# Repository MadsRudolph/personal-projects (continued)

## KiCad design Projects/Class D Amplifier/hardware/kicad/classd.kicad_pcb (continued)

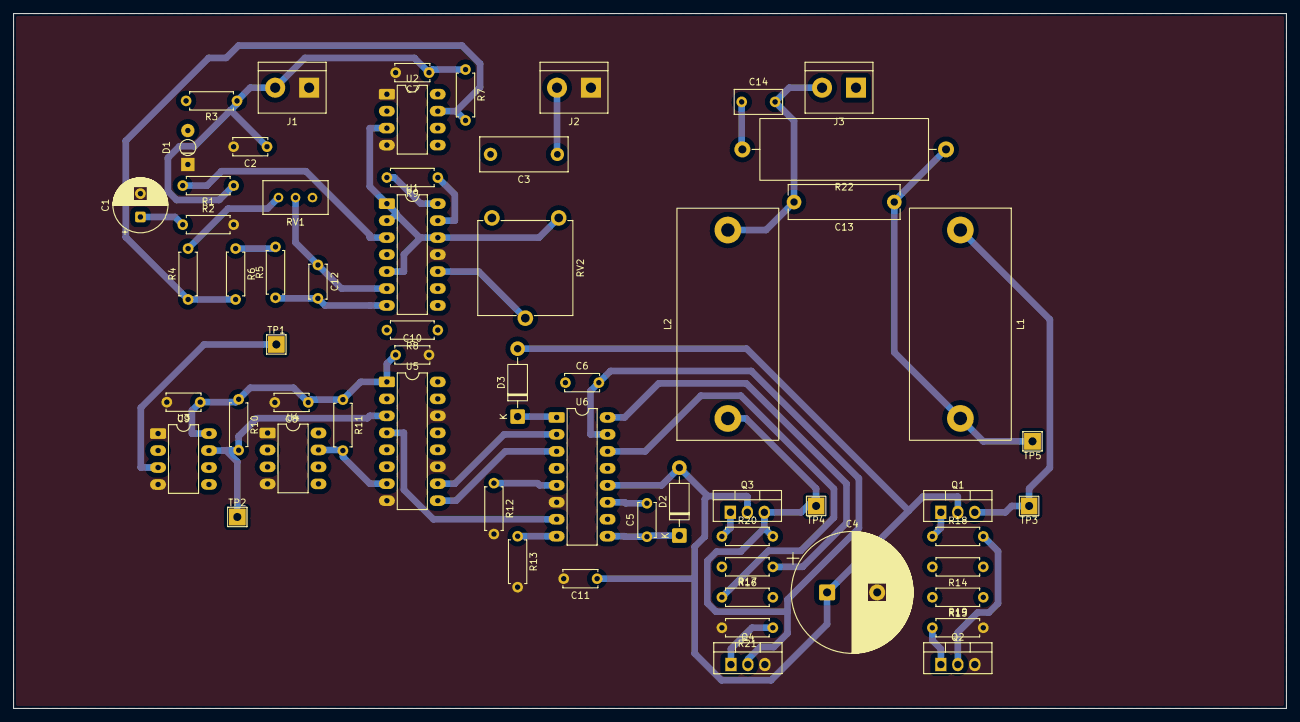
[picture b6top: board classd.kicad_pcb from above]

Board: 2 copper layers, 190.5 x 104.0 mm, 61 parts (0 on the bottom side), 39 nets.

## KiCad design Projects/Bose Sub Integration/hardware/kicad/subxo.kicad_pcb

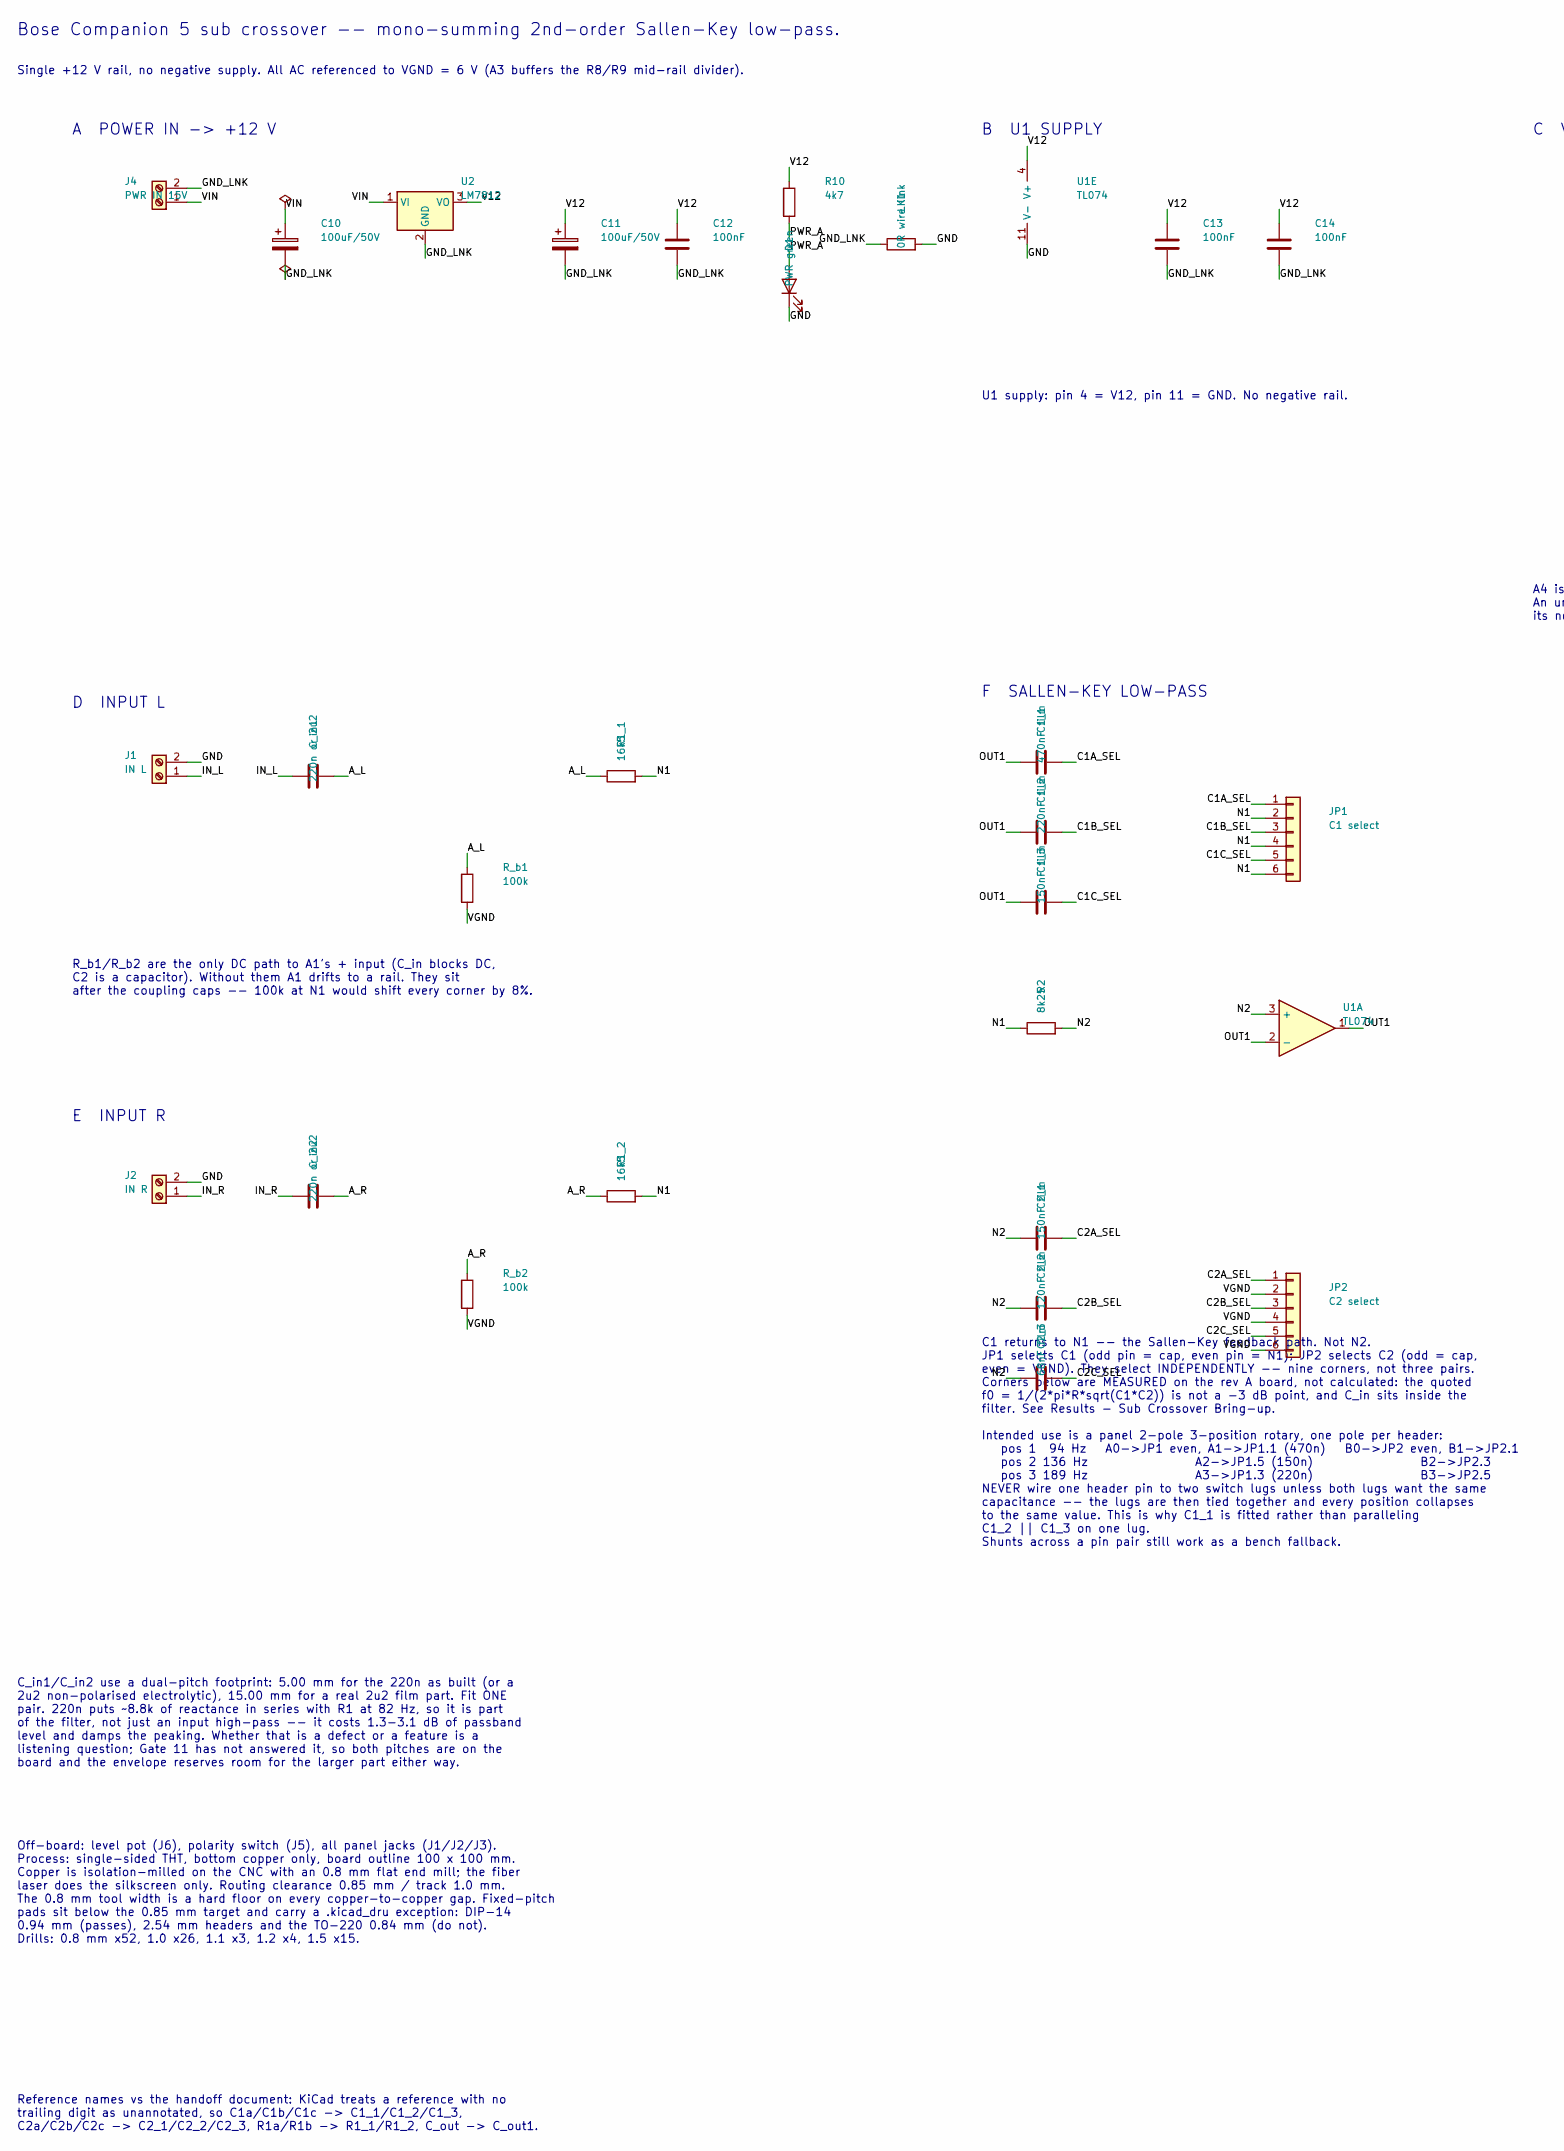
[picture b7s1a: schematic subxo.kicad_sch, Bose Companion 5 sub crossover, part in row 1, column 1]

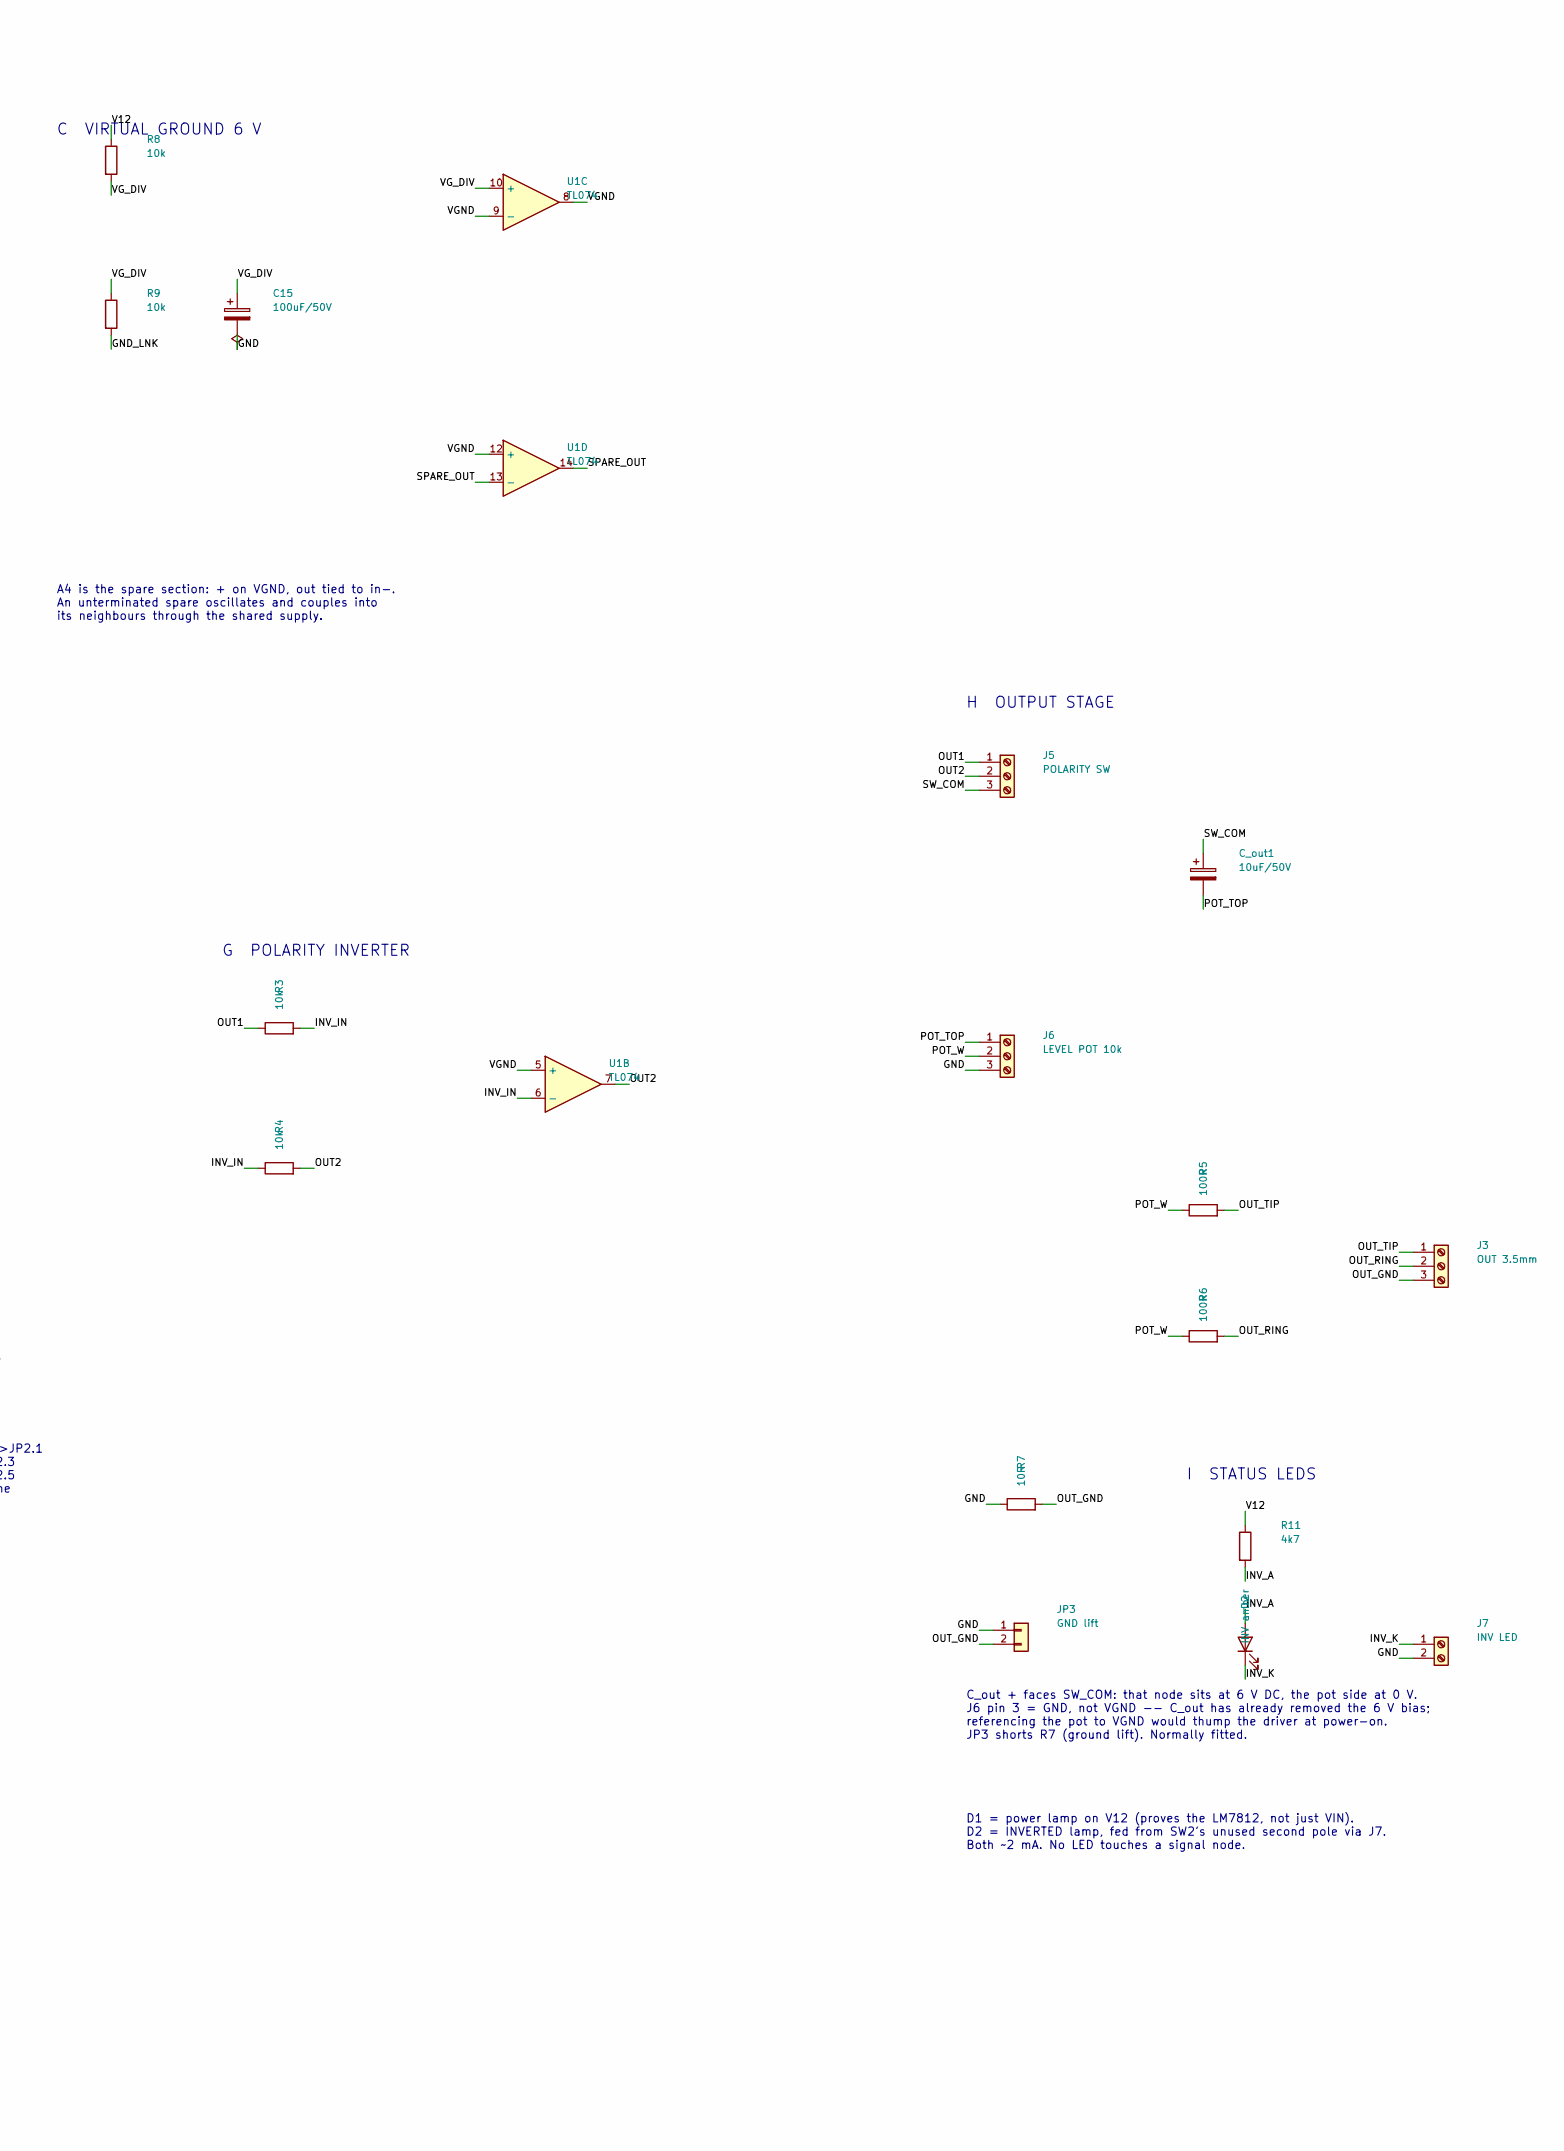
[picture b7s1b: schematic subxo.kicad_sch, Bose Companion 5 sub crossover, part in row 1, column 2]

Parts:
C1_1: 470nF film; C_Rect_L7.2mm_W3.0mm_P5.00mm_FKS2_FKP2_MKS2_MKP2
C1_2: 220nF film; C_Rect_L18.0mm_W7.0mm_P15.00mm_FKS3_FKP3
C1_3: 150nF film; C_Rect_L11.0mm_W4.2mm_P10.00mm_MKT
C2_1: 150nF film; C_Rect_L7.2mm_W5.5mm_P5.00mm_FKS2_FKP2_MKS2_MKP2
C2_2: 120nF film; C_Rect_L13.0mm_W4.0mm_P10.00mm_FKS3_FKP3_MKS4
C2_3: 68nF film; C_Rect_L7.2mm_W5.5mm_P5.00mm_FKS2_FKP2_MKS2_MKP2
C10, C11, C15: 100uF/50V; CP_Radial_D10.0mm_P5.00mm
C12, C13, C14: 100nF; C_Disc_D5.0mm_W2.5mm_P5.00mm
C_in1, C_in2: 220n or 2u2; C_Rect_L18.0mm_W9.0mm_P15.00mm_FKS3_FKP3
C_out1: 10uF/50V; CP_Radial_D8.0mm_P3.50mm
D1: PWR green; LED_D3.0mm
D2: INV amber; LED_D3.0mm
J1: IN L; TerminalBlock_bornier-2_P5.08mm
J2: IN R; TerminalBlock_bornier-2_P5.08mm
J3: OUT 3.5mm; TerminalBlock_bornier-3_P5.08mm
J4: PWR IN 15V; TerminalBlock_bornier-2_P5.08mm
J5: POLARITY SW; TerminalBlock_bornier-3_P5.08mm
J6: LEVEL POT 10k; TerminalBlock_bornier-3_P5.08mm
J7: INV LED; TerminalBlock_bornier-2_P5.08mm
JP1: C1 select; PinHeader_1x06_P2.54mm_Vertical
JP2: C2 select; PinHeader_1x06_P2.54mm_Vertical
JP3: GND lift; PinHeader_1x02_P2.54mm_Vertical
LK1: 0R wire link; WireLink_P14.50mm
R1_1, R1_2: 16k5; R_Axial_DIN0207_L6.3mm_D2.5mm_P7.62mm_Horizontal
R2: 8k25; R_Axial_DIN0207_L6.3mm_D2.5mm_P7.62mm_Horizontal
R3, R4, R8, R9: 10k; R_Axial_DIN0207_L6.3mm_D2.5mm_P7.62mm_Horizontal
R5, R6: 100R; R_Axial_DIN0207_L6.3mm_D2.5mm_P7.62mm_Horizontal
R7: 10R; R_Axial_DIN0207_L6.3mm_D2.5mm_P7.62mm_Horizontal
R10, R11: 4k7; R_Axial_DIN0207_L6.3mm_D2.5mm_P7.62mm_Horizontal
R_b1, R_b2: 100k; R_Axial_DIN0207_L6.3mm_D2.5mm_P7.62mm_Horizontal
U1: TL074; DIP-14_W7.62mm_LongPads
U2: LM7812; TO-220-3_Vertical_LaserPads

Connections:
/A_L: C_in1.2, R1_1.1, R_b1.1
/A_R: C_in2.2, R1_2.1, R_b2.1
/C1A_SEL: C1_1.2, JP1.1
/C1B_SEL: C1_2.2, JP1.3
/C1C_SEL: C1_3.2, JP1.5
/C2A_SEL: C2_1.2, JP2.1
/C2B_SEL: C2_2.2, JP2.3
/C2C_SEL: C2_3.2, JP2.5
/GND: C15.2, D1.1 (K), J1.2, J2.2, J6.3, J7.2, JP3.1, LK1.2, R7.1, U1.11 (V-)
/GND_LNK: C10.2, C11.2, C12.2, C13.2, C14.2, J4.2, LK1.1, R9.2, U2.2 (GND)
/INV_A: D2.2 (A), R11.2
/INV_IN: R3.2, R4.1, U1.6 (-)
/INV_K: D2.1 (K), J7.1
/IN_L: C_in1.1, J1.1
/IN_R: C_in2.1, J2.1
/N1: JP1.2, JP1.4, JP1.6, R1_1.2, R1_2.2, R2.1
/N2: C2_1.1, C2_2.1, C2_3.1, R2.2, U1.3 (+)
/OUT1: C1_1.1, C1_2.1, C1_3.1, J5.1, R3.1, U1.1, U1.2 (-)
/OUT2: J5.2, R4.2, U1.7
/OUT_GND: J3.3, JP3.2, R7.2
/OUT_RING: J3.2, R6.2
/OUT_TIP: J3.1, R5.2
/POT_TOP: C_out1.2, J6.1
/POT_W: J6.2, R5.1, R6.1
/PWR_A: D1.2 (A), R10.2
/SPARE_OUT: U1.13 (-), U1.14
/SW_COM: C_out1.1, J5.3
/V12: C11.1, C12.1, C13.1, C14.1, R8.1, R10.1, R11.1, U1.4 (V+), U2.3 (VO)
/VGND: JP2.2, JP2.4, JP2.6, R_b1.2, R_b2.2, U1.5 (+), U1.8, U1.9 (-), U1.12 (+)
/VG_DIV: C15.1, R8.2, R9.1, U1.10 (+)
/VIN: C10.1, J4.1, U2.1 (VI)

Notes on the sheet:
Bose Companion 5 sub crossover -- mono-summing 2nd-order Sallen-Key low-pass.
Single +12 V rail, no negative supply. All AC referenced to VGND = 6 V (A3 buffers the R8/R9 mid-rail divider).
A POWER IN -> +12 V
B U1 SUPPLY
C VIRTUAL GROUND 6 V
D INPUT L
E INPUT R
F SALLEN-KEY LOW-PASS
G POLARITY INVERTER
H OUTPUT STAGE
I STATUS LEDS
U1 supply: pin 4 = V12, pin 11 = GND. No negative rail.
A4 is the spare section: + on VGND, out tied to in-. An unterminated spare oscillates and couples into its neighbours through the shared supply.
R_b1/R_b2 are the only DC path to A1's + input (C_in blocks DC, C2 is a capacitor). Without them A1 drifts to a rail. They sit after the coupling caps -- 100k at N1 would shift every corner by 8%.
C1 returns to N1 -- the Sallen-Key feedback path. Not N2. JP1 selects C1 (odd pin = cap, even pin = N1); JP2 selects C2 (odd = cap, even = VGND). They select INDEPENDENTLY -- nine corners, not three pairs. Corners below are MEASURED on the rev A board, not calculated: the quoted f0 = 1/(2*pi*R*sqrt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
C_in1/C_in2 use a dual-pitch footprint: 5.00 mm for the 220n as built (or a 2u2 non-polarised electrolytic), 15.00 mm for a real 2u2 film part. Fit ONE pair. 220n puts ~8.8k of reactance in series with R1 at 82 Hz, so it is part of the filter, not just an input high-pass -- it costs 1.3-3.1 dB of p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
D1 = power lamp on V12 (proves the LM7812, not just VIN). D2 = INVERTED lamp, fed from SW2's unused second pole via J7. Both ~2 mA. No LED touches a signal node.
C_out + faces SW_COM: that node sits at 6 V DC, the pot side at 0 V. J6 pin 3 = GND, not VGND -- C_out has already removed the 6 V bias; referencing the pot to VGND would thump the driver at power-on. JP3 shorts R7 (ground lift). Normally fitted.
Off-board: level pot (J6), polarity switch (J5), all panel jacks (J1/J2/J3). Process: single-sided THT, bottom copper only, board outline 100 x 100 mm. Copper is isolation-milled on the CNC with an 0.8 mm flat end mill; the fiber laser does the silkscreen only. Routing clearance 0.85 mm / track 1.0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
Reference names vs the handoff document: KiCad treats a reference with no trailing digit as unannotated, so C1a/C1b/C1c -> C1_1/C1_2/C1_3, C2a/C2b/C2c -> C2_1/C2_2/C2_3, R1a/R1b -> R1_1/R1_2, C_out -> C_out1.

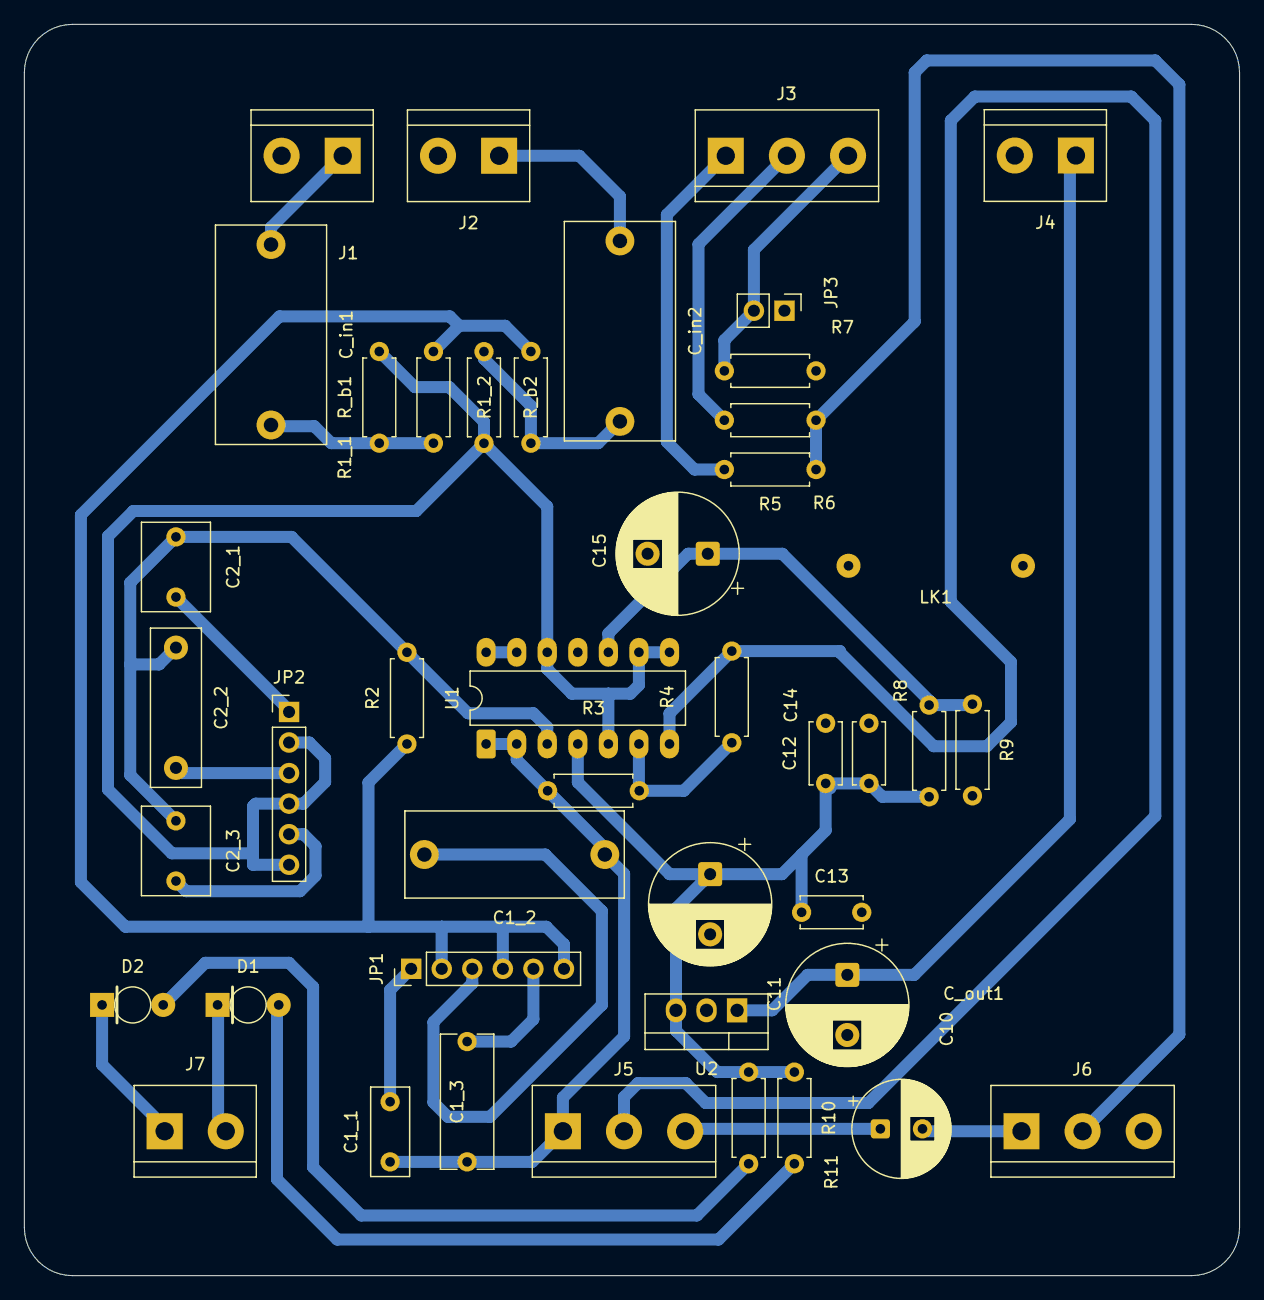
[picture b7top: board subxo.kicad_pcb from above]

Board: 2 copper layers, 101.0 x 104.0 mm, 44 parts (0 on the bottom side), 31 nets.

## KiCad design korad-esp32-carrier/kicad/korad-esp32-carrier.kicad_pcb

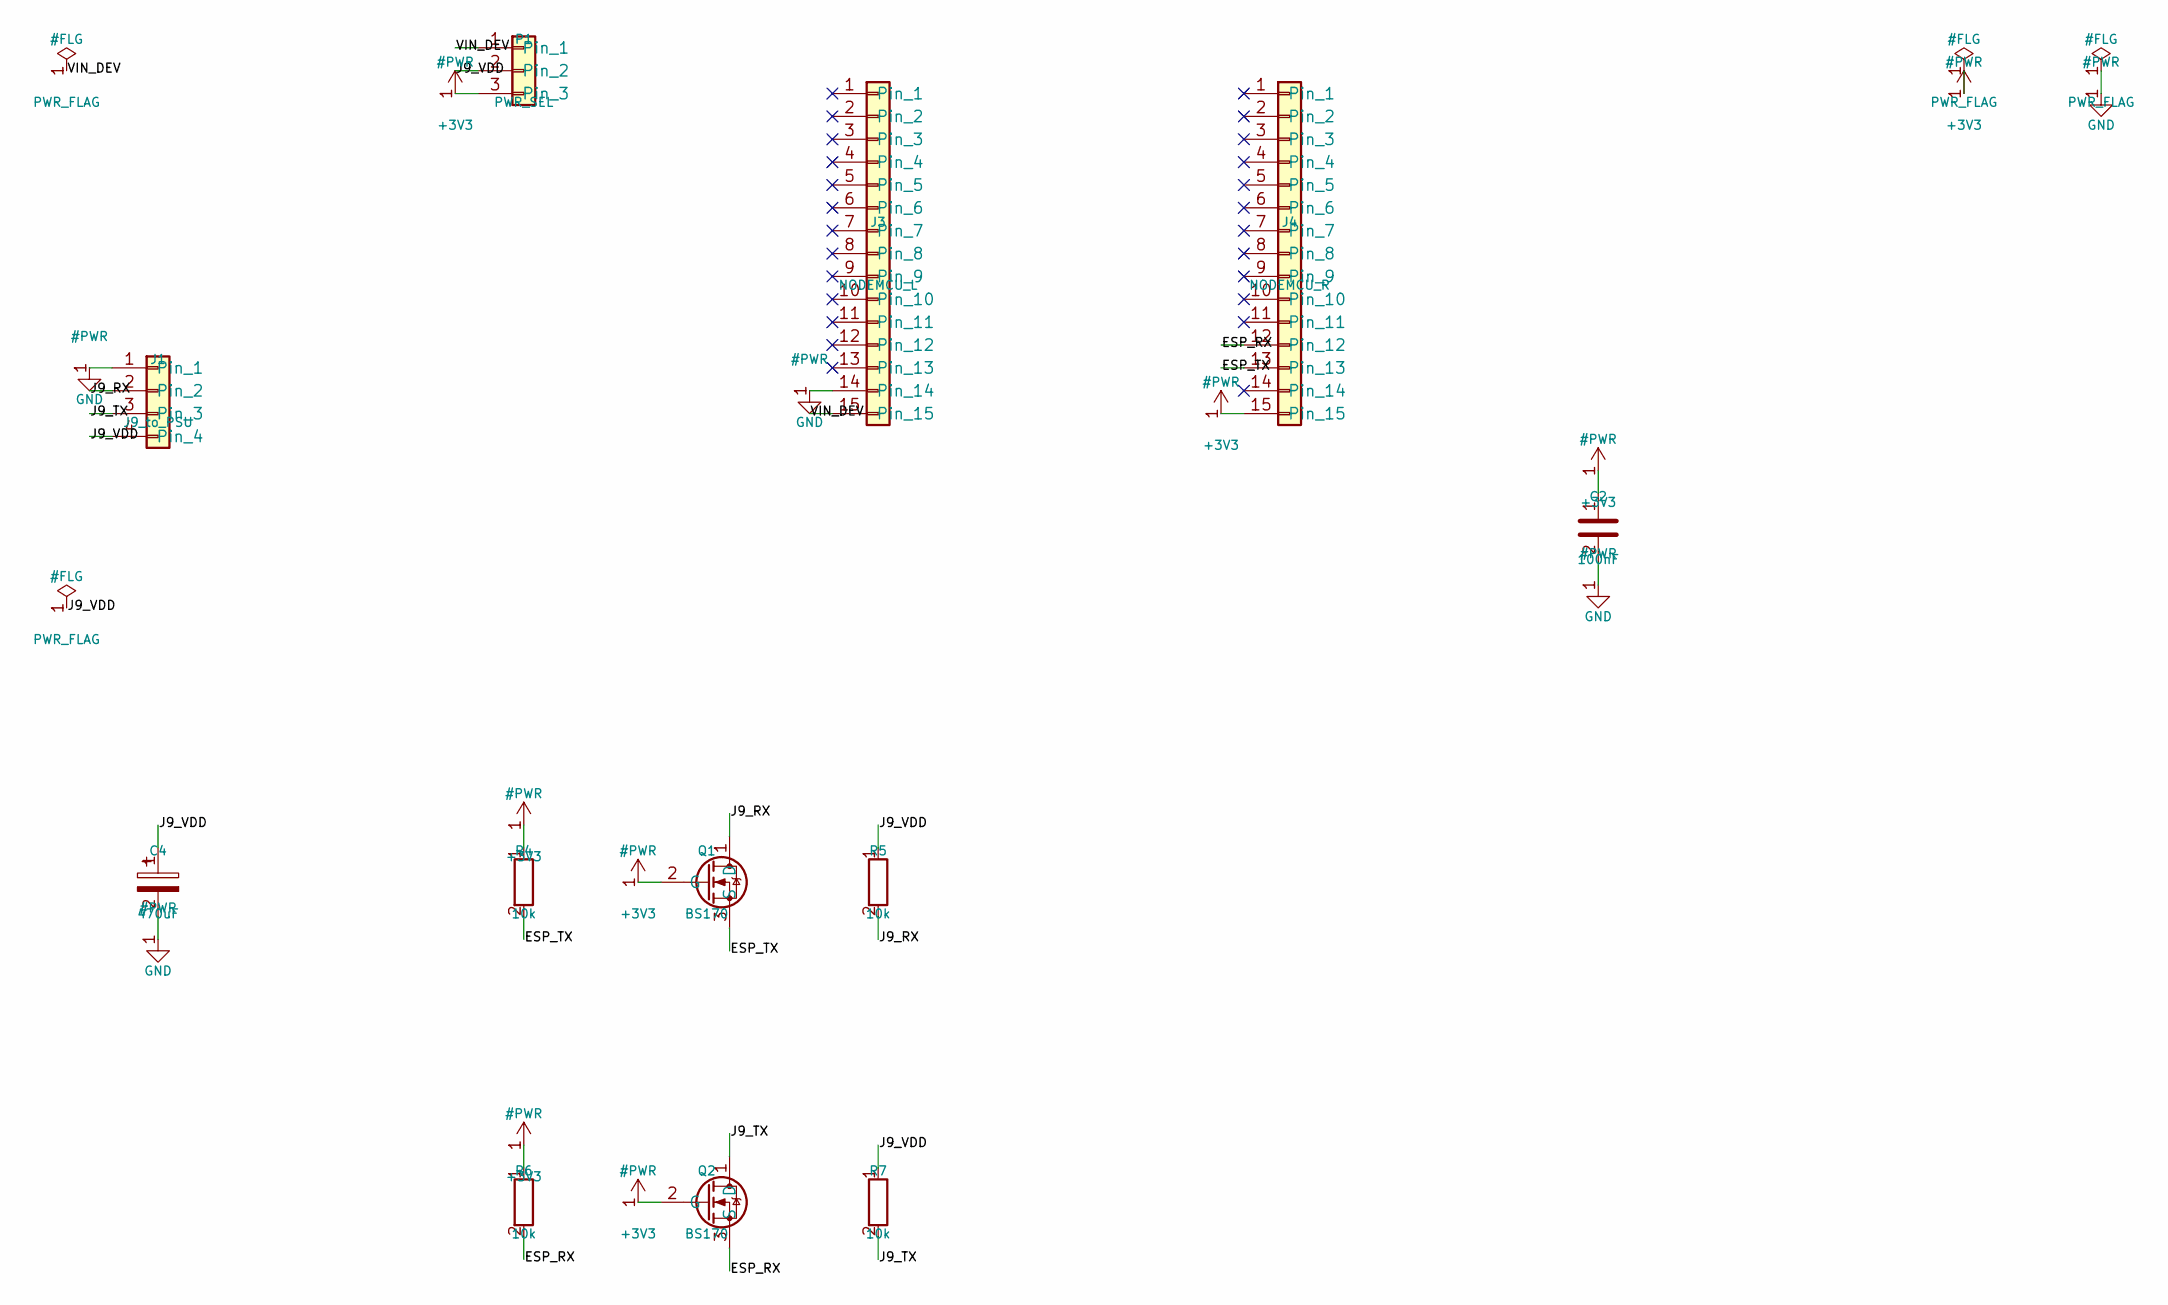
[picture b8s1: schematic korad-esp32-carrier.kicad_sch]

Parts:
C2: 100nF; C_Disc_D5.0mm_W2.5mm_P5.00mm
C4: 470uF; CP_Radial_D10.0mm_P5.00mm
J1: J9_to_PSU; PinHeader_1x04_P2.54mm_Vertical
J3: NODEMCU_L; PinSocket_1x15_P2.54mm_Vertical
J4: NODEMCU_R; PinSocket_1x15_P2.54mm_Vertical
P1: PWR_SEL; PinHeader_1x03_P2.54mm_Vertical
Q1, Q2: BS170; TO-92_Inline_Wide
R4, R5, R6, R7: 10k; R_Axial_DIN0207_L6.3mm_D2.5mm_P7.62mm_Horizontal

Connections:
+3V3: C2.1, J4.15, P1.3, Q1.2 (G), Q2.2 (G), R4.1, R6.1
/ESP_RX: J4.12, Q2.3 (S), R6.2
/ESP_TX: J4.13, Q1.3 (S), R4.2
/J9_RX: J1.2, Q1.1 (D), R5.2
/J9_TX: J1.3, Q2.1 (D), R7.2
/J9_VDD: C4.1, J1.4, P1.2, R5.1, R7.1
/VIN_DEV: J3.15, P1.1
GND: C2.2, C4.2, J1.1, J3.14

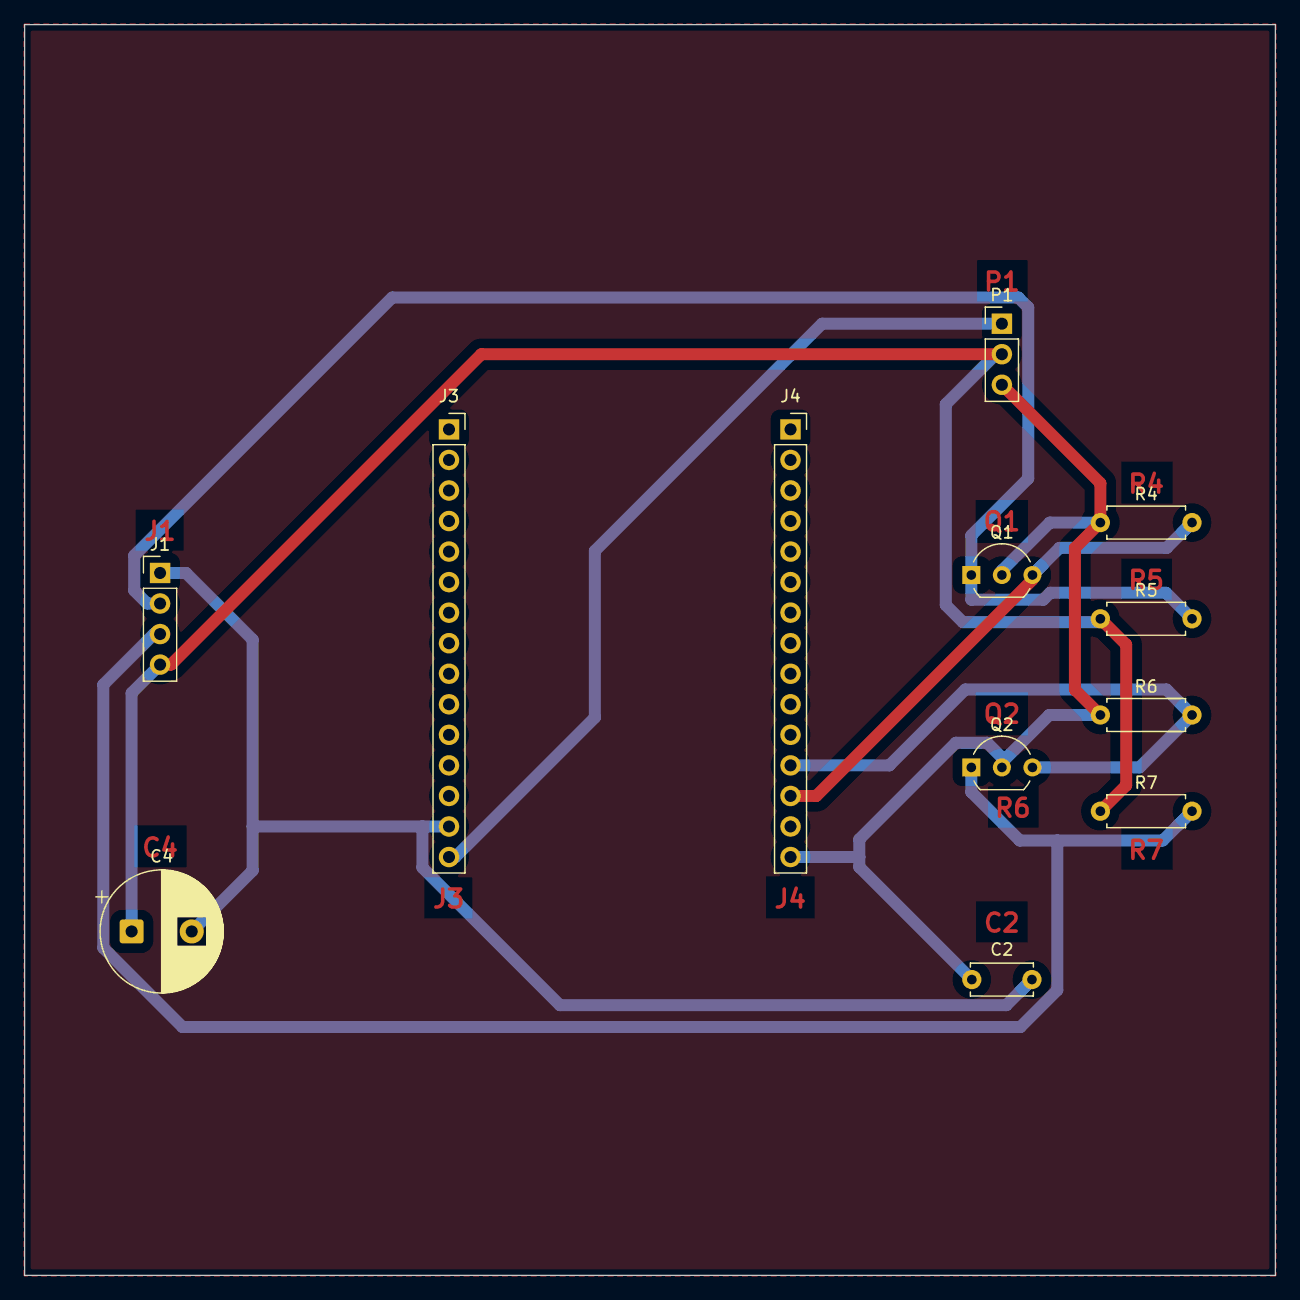
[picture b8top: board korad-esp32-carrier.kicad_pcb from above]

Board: 2 copper layers, 104.0 x 104.0 mm, 12 parts (0 on the bottom side), 8 nets.

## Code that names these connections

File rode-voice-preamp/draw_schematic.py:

#!/usr/bin/env python3
"""Draws rode-preamp.kicad_sch: VideoMic GO -> LM358 x564 -> Uno A0.

Re-run to regenerate the schematic (close KiCad first):
    python3 draw_schematic.py
Uses the kicad-schematic skill's schdraw/idioms.
"""
import os
import sys

sys.path.insert(0, os.path.expanduser("~/.claude/skills/kicad-schematic/scripts"))
from schdraw import Sheet  # noqa: E402
import idioms as I  # noqa: E402

HERE = os.path.dirname(os.path.abspath(__file__))
OUT = os.path.join(HERE, "rode-preamp.kicad_sch")
PRO = os.path.join(HERE, "rode-preamp.kicad_pro")


def G(n):
    return round(n * 1.27, 2)


OP = "Amplifier_Operational:LM358"
FP_R = "Resistor_THT:R_Axial_DIN0207_L6.3mm_D2.5mm_P7.62mm_Horizontal"
FP_C = "Capacitor_THT:C_Disc_D5.0mm_W2.5mm_P5.00mm"
FP_CP = "Capacitor_THT:CP_Radial_D5.0mm_P2.50mm"        # 10u 50V, leads bent 2.0 -> 2.5 mm
FP_DIP = "Package_DIP:DIP-8_W7.62mm_LongPads"
FP_J1 = "TerminalBlock_Phoenix:TerminalBlock_Phoenix_MKDS-1,5-2_1x02_P5.00mm_Horizontal"
FP_J2 = "Connector_PinHeader_2.54mm:PinHeader_1x04_P2.54mm_Vertical"  # Molex KK male fits

sh = Sheet(paper="A4", title="RØDE VideoMic GO preamp for Arduino Uno A0",
           project="rode-preamp", project_file=PRO if os.path.exists(PRO) else None)


def offset(lib, pin, **kw):
    """Where `pin` sits relative to the part origin (measured on a scratch sheet)."""
    s = Sheet(paper="A4")
    p = s.place(lib, "X1", at=(G(100), G(100)), **kw)
    q = p.pin(pin)
    return q.x - G(100), q.y - G(100)


def place_pin(lib, ref, pin, target, **kw):
    dx, dy = offset(lib, pin, **{k: v for k, v in kw.items() if k in ("rot", "mirror", "unit")})
    return sh.place(lib, ref, at=(round(target[0] - dx, 2), round(target[1] - dy, 2)), **kw)


Y = G(48)                     # signal line into stage A
TY = Y - G(16)                # block titles

# ---------------------------------------------------------------- mic in + plug-in power
j1 = place_pin("Connector:Screw_Terminal_01x02", "J1", "1", (G(20), Y), mirror="y",
               value="MIC IN", footprint=FP_J1)
M = (G(34), Y)
sh.seg(j1.pin(1), M)
sh.gnd(j1.pin(2), drop=G(4))
r1 = sh.place("Device:R", "R1", at=(G(34), Y - G(7)), value="2.2k", footprint=FP_R)
sh.seg(r1.pin(2), M)
sh.rail(r1.pin(1), net="+3V3", rise=G(2))
sh.label((G(28), Y), "MIC")
c1 = sh.place("Device:C_Polarized", "C1", at=(G(44), Y), rot=90, value="10u", footprint=FP_CP)
sh.seg(M, c1.pin(1))
N = (G(54), Y)
sh.seg(c1.pin(2), N)
r2 = sh.place("Device:R", "R2", at=(G(54), Y + G(7)), value="100k", footprint=FP_R)
sh.seg(N, r2.pin(1))
sh.seg(r2.pin(2), (G(54), Y + G(14)))
sh.label((G(54), Y + G(14)), "BIAS", rot=270)
sh.note((G(14), TY), "Mic in + plug-in power", size=1.8)


# ---------------------------------------------------------------- gain stages
def stage(plus_x, y, refs, vals, unit, title):
    """Non-inverting stage, AC-coupled gain leg: gain = 1 + Rf/Rg above the Rg-C corner."""
    u = sh.place(OP, "U1", unit=unit, at=(plus_x + G(6), y + G(2)), value="LM358", footprint=FP_DIP)
    mx, out = plus_x, u.pin("out")
    yfb = y + G(13)
    yc = yfb + G(8)
    rx = out.x + G(4)
    rf = sh.place("Device:R", refs["Rf"], at=(mx + G(6), yfb), rot=90, value=vals["Rf"], footprint=FP_R)
    cf = sh.place("Device:C", refs["Cf"], at=(mx + G(6), yc), rot=90, value=vals["Cf"], footprint=FP_C)
    rg = sh.place("Device:R", refs["Rg"], at=(mx - G(7), yfb), rot=90, value=vals["Rg"], footprint=FP_R)
    cg = sh.place("Device:C_Polarized", refs["Cg"], at=(mx - G(14), yfb + G(5)), value="10u", footprint=FP_CP)
    sh.seg(u.pin("-"), (mx, yfb))
    sh.seg((mx, yfb), rf.pin(1))
    sh.seg((mx, yfb), (mx, yc))
    sh.seg((mx, yc), cf.pin(1))
    sh.seg(rf.pin(2), (rx, yfb))
    sh.seg(cf.pin(2), (rx, yc))
    sh.seg((rx, yc), (rx, yfb))
    sh.seg((rx, yfb), (rx, out.y))
    sh.seg(rg.pin(2), (mx, yfb))
    sh.seg(rg.pin(1), (mx - G(14), yfb))
    sh.seg((mx - G(14), yfb), cg.pin(1))
    sh.gnd(cg.pin(2), drop=G(3))
    sh.note((mx - G(16), TY), title, size=1.8)
    return u, out, rx


ua, outa, rxa = stage(G(84), Y, {"Rf": "R6", "Cf": "C4", "Rg": "R5", "Cg": "C3"},
                      {"Rf": "100k", "Cf": "220p", "Rg": "1.01k"}, 1, "Stage A  x100  (1 + 100k/1.01k)")
sh.seg(N, ua.pin("+"))
YB = outa.y
ub, outb, rxb = stage(G(130), YB, {"Rf": "R8", "Cf": "C6", "Rg": "R7", "Cg": "C5"},
                      {"Rf": "46.4k", "Cf": "470p", "Rg": "10k"}, 2, "Stage B  x5.6  (1 + 46.4k/10k)")
sh.seg(outa, ub.pin("+"))
sh.label((rxa + G(4), outa.y), "OUT_A")

# ---------------------------------------------------------------- anti-alias RC + Uno header
r9 = sh.place("Device:R", "R9", at=(G(160), outb.y), rot=90, value="1.01k", footprint=FP_R)
sh.seg(outb, (rxb, outb.y))
sh.seg((rxb, outb.y), r9.pin(1))
sh.label((rxb + G(2), outb.y), "OUT_B")
O = (G(170), outb.y)
sh.seg(r9.pin(2), O)
c7 = sh.place("Device:C", "C7", at=(G(170), outb.y + G(7)), value="10n", footprint=FP_C)
sh.seg(O, c7.pin(1))
sh.gnd(c7.pin(2), drop=G(3))
# header order 3V3, 5V, A0, GND: 5V and A0 leave adjacent LM358 pins (8, 7), so they sit
# side by side on the header too and GND stays outside them -- keeps the board one-layer
j2 = place_pin("Connector_Generic:Conn_01x04", "J2", "3", (G(190), outb.y), value="TO UNO", footprint=FP_J2)
sh.seg(O, j2.pin(3))
sh.label((G(176), outb.y), "A0")
p1, p2, p4 = j2.pin(1), j2.pin(2), j2.pin(4)
top = p1.y - G(6)
sh.seg(p1, (G(183), p1.y)); sh.seg((G(183), p1.y), (G(183), top))
sh.rail((G(183), top), net="+3V3", rise=G(2))
sh.seg(p2, (G(178), p2.y)); sh.seg((G(178), p2.y), (G(178), top))
sh.rail((G(178), top), net="+5V", rise=G(2))
sh.seg(p4, (G(184), p4.y))
sh.gnd((G(184), p4.y), drop=G(3))
sh.note((G(158), TY), "Anti-alias RC + Uno header", size=1.8)

# connector-fed rails: tell ERC they are driven
FY = Y + G(62)
for i, net in enumerate(("+5V", "+3V3", "GND")):
    a = (G(180) + i * G(13), FY)
    b = (a[0] + G(5), FY)
    sh.seg(a, b)
    if net == "GND":
        sh.gnd(a, drop=G(2))
    else:
        sh.rail(a, net=net, rise=G(2))
    sh.power("power:PWR_FLAG", b)
sh.note((G(178), FY - G(9)), "Rails come in on J2", size=1.8)

# ---------------------------------------------------------------- bias + op-amp supply
vg = I.virtual_ground_divider(sh, (G(20), Y + G(30)), refs={"R1": "R3", "R2": "R4", "C": "C2"},
                              values={"R1": "100k", "R2": "56.2k", "C": "10u"}, rail="+5V",
                              title="Bias 1.8 V  (5V x 56.2k/156.2k)")
sh.label(vg["out"], "BIAS")
sup = I.opamp_supply(sh, (G(140), Y + G(54)), refs={"U": "U1", "Cp": "C8"}, values={"Cp": "100n"},
                     opamp=OP, unit=3, pos="+5V", title="LM358 supply, 100n at pin 8")
for p in sh.parts:
    if p.ref in ("R3", "R4"):
        p.footprint = FP_R
    elif p.ref == "C2":
        p.footprint = FP_CP
    elif p.ref == "C8":
        p.footprint = FP_C
    elif p.ref == "U1":
        p.footprint = FP_DIP

TARGET = {
    "MIC": {("J1", "1"), ("R1", "2"), ("C1", "1")},
    "+3V3": {("R1", "1"), ("J2", "1")},
    "IN_A": {("C1", "2"), ("R2", "1"), ("U1", "3")},
    "BIAS": {("R2", "2"), ("R3", "2"), ("R4", "1"), ("C2", "1")},
    "+5V": {("R3", "1"), ("U1", "8"), ("C8", "1"), ("J2", "2")},
    "GND": {("J1", "2"), ("R4", "2"), ("C2", "2"), ("C3", "2"), ("C5", "2"), ("C7", "2"),
            ("C8", "2"), ("U1", "4"), ("J2", "4")},
    "FB_A": {("U1", "2"), ("R5", "2"), ("R6", "1"), ("C4", "1")},
    "RG_A": {("R5", "1"), ("C3", "1")},
    "OUT_A": {("U1", "1"), ("R6", "2"), ("C4", "2"), ("U1", "5")},
    "FB_B": {("U1", "6"), ("R7", "2"), ("R8", "1"), ("C6", "1")},
    "RG_B": {("R7", "1"), ("C5", "1")},
    "OUT_B": {("U1", "7"), ("R8", "2"), ("C6", "2"), ("R9", "1")},
    "A0": {("R9", "2"), ("C7", "1"), ("J2", "3")},
}

if __name__ == "__main__":
    probs = sh.check()
    for p in probs:
        print("CHECK:", p)
    ok = sh.verify_against(TARGET)
    print("netlist", "OK" if ok else "MISMATCH")
    if ok:
        sh.emit(OUT)
        print("wrote", OUT)
